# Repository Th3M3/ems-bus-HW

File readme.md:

### EMS Bus Level Shifter PCB

##### Stückliste:

| Bez.| Typ        | Bauform  | Reichelt.de Bezeichnung                         | Artikel-Nr.       |
| --- | ---------- | -------- | ------------------------------------------------ | ----------------- |
| C1  | 68p/50V    | G0603    | SMD-Kerko, 0603, 68pF, 50V, 5%, MLCC             | NPO 0603 BF 68P   |
| C2  | 10µ/25V    | G0603    | SMD-Vielschichtkondensator G0603 - 10µF 25V      | X5R-G0603 10/25   |
| C3  | 1n/50V     | G0603    | SMD-Kerko, 0603, 1,0nF, 50V, 10%, MLCC           | X7R 0603 CF 1,0N  |
| C4  | 1.5n/50V   | G0603    | SMD-Kerko, 0603, 1,5nF, 50V, 10%, MLCC           | X7R 0603 CF 1,5N  |
| C5  | 10n/50V    | G0603    | SMD-Vielschicht-Keramikkondensator 10N, 10%      | X7R-G0603 10N     |
| C6  | 100n/50V   |G0603     | SMD-Kerko, 0603, 100nF, 50V, 10%, MLCC, FT-Cap   | X7R 0603FCF 100N  |
| D1  | BAT42      | MINIMELF | Schottkydiode, 30 V, 0,2 A, Mini Melf            | BAT 42 SMD        |
| D2  | BAT42      | MINIMELF | Schottkydiode, 30 V, 0,2 A, Mini Melf            | BAT 42 SMD        |
| D3  | BAT42      | MINIMELF | Schottkydiode, 30 V, 0,2 A, Mini Melf            | BAT 42 SMD        |
| D4  | BAT42      | MINIMELF | Schottkydiode, 30 V, 0,2 A, Mini Melf            | BAT 42 SMD        |
| D5  | BAT42      | MINIMELF | Schottkydiode, 30 V, 0,2 A, Mini Melf            | BAT 42 SMD        |
| D6  | 1N4148     | MINIMELF | Gleichrichterdiode, 100 V, 0,15 A, Mini Melf     | 1N 4148 SMD       |
| F1  | 30V/150mA  | 1210     | Rückstellende Sicherungen, 30 V, 150 mA          | LITT MICROSMD005  |
| F2  | 30V/150mA  | 1210     | Rückstellende Sicherungen, 30 V, 150 mA          | LITT MICROSMD005  |
| IC1 | LM393 SMD  | SOIC-8   | Komparator, 2-fach, SO-8                         | LM 393 D SMD      |
| L1  | 4,7µH      | 1206     | SMD-Induktivität, 1206, Ferrit, 4,7µ             | L-1206F 4,7µ      |
| L2  | 4,7µH      | 1206     | SMD-Induktivität, 1206, Ferrit, 4,7µ             | L-1206F 4,7µ      |
| R1  | 10k        | R0805    | SMD-Widerstand, 0805, 10 kOhm, 125 mW, 1%        | RND 0805 1 10K    |
| R2  | 360R       | R0805    | SMD-Widerstand, 0805, 360 Ohm, 125 mW, 1%        | RND 0805 1 360    |
| R3  | 47k        | R0805    | SMD-Widerstand, 0805, 47 kOhm, 125 mW, 1%        | RND 0805 1 47K    |
| R5  | 100k       | R0805    | SMD-Widerstand, 0805, 100 kOhm, 125 mW, 1%       | RND 0805 1 100K   |
| R6  | 4.7k       | R0805    | SMD-Widerstand, 0805, 4,7 kOhm, 125 mW, 1%       | RND 0805 1 4,7K   |
| R7  | 100R       | R0805    | SMD-Widerstand, 0805, 100 Ohm, 125 mW, 1%        | RND 0805 1 100    |
| R8  | 910R       | R0805    | SMD-Widerstand, 0805, 910 Ohm, 125 mW, 1%        | RND 0805 1 910    |
| R9  | 910R       | R0805    | SMD-Widerstand, 0805, 910 Ohm, 125 mW, 1%        | RND 0805 1 910    |
| R10 | 910R       | R0805    | SMD-Widerstand, 0805, 910 Ohm, 125 mW, 1%        | RND 0805 1 910    |
| R11 | 910R       | R0805    | SMD-Widerstand, 0805, 910 Ohm, 125 mW, 1%        | RND 0805 1 910    |
| R12 | 4.7k       | R0805    | SMD-Widerstand, 0805, 4,7 kOhm, 125 mW, 1%       | RND 0805 1 4,7K   |
| T1  | BC847B     | SOT-23   | Bipolartransistor, NPN, 45V, 0,1A, 0,25W, SOT-23 | BC 847B INF       |

---
##### Changelog:
- v2:
   * verbesserte Teileplazierung auf der Platine
   * breitere Leiterbahnen an der Thermal Pads
   * größere Schrift 'EMS Bus Level Shifter'

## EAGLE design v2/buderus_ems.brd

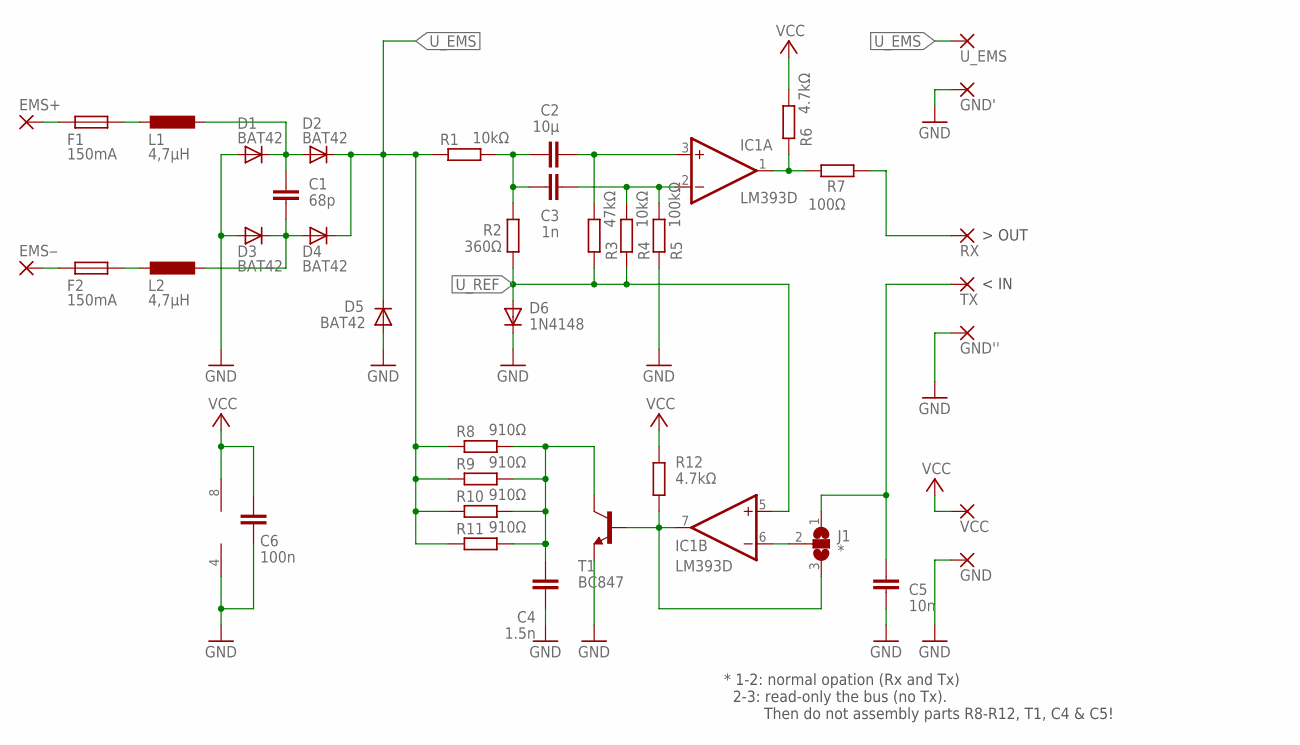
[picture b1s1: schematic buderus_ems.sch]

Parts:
C1: 68p; C0603
C2: 10µ; C0603
C3: 1n; C0603
C4: 1.5n; C0603
C5: 10n; C0603
C6: 100n; C0603
D1, D2, D3, D4, D5: BAT42; MINIMELF
D6: 1N4148; MINIMELF
EMS+: WIREPAD2,15/1,0; 2,15/1,0
EMS‒: WIREPAD2,15/1,0; 2,15/1,0
F1, F2: 150mA; R1210
GND: WIREPAD2,15/1,0; 2,15/1,0
GND': WIREPAD2,15/1,0; 2,15/1,0
GND'': WIREPAD2,15/1,0; 2,15/1,0
IC1: LM393D; SO08
J1: *; SJ_2
L1, L2: 4,7µH; L3216C
R1, R4: 10kΩ; R0805
R2: 360Ω; R0805
R3: 47kΩ; R0805
R5: 100kΩ; R0805
R6, R12: 4.7kΩ; R0805
R7: 100Ω; R0805
R8, R9, R10, R11: 910Ω; R0805
RX: WIREPAD2,15/1,0; 2,15/1,0
T1: BC847; SOT23
TX: WIREPAD2,15/1,0; 2,15/1,0
U_EMS: WIREPAD2,15/1,0; 2,15/1,0
VCC: WIREPAD2,15/1,0; 2,15/1,0

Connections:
EMS_1: C1.2, D1.C, D2.A, L1.2
EMS_2: C1.1, D3.C, D4.A, L2.2
EMS_RX: R7.1, RX.1
EMS_TX: C5.2, J1.1, TX.1
GND: C4.1, C5.1, C6.1, D1.A, D3.A, D5.A, D6.C, GND.1, GND'.1, GND''.1, IC1.4 (V-), R5.1, T1.2 (E)
unnamed: IC1.7 (OUT), J1.3, R12.1, T1.1 (B)
unnamed: IC1.6 (-IN), J1.2
unnamed: C3.2, IC1.2 (-IN), R4.2, R5.2
unnamed: C2.2, IC1.3 (+IN), R3.2
unnamed: IC1.1 (OUT), R6.1, R7.2
unnamed: EMS+.1, F1.1
unnamed: EMS‒.1, F2.1
unnamed: C4.2, R8.2, R9.2, R10.2, R11.2, T1.3 (C)
unnamed: F1.2, L1.1
unnamed: F2.2, L2.1
unnamed: C2.1, C3.1, R1.2, R2.2
U_EMS: D2.C, D4.C, D5.C, R1.1, R8.1, R9.1, R10.1, R11.1, U_EMS.1
U_REF: D6.A, IC1.5 (+IN), R2.1, R3.1, R4.1
VCC: C6.2, IC1.8 (V+), R6.2, R12.2, VCC.1

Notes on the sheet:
* 1-2: normal opation (Rx and Tx) 2-3: read-only the bus (no Tx). Then do not assembly parts R8-R12, T1, C4 & C5!
< IN

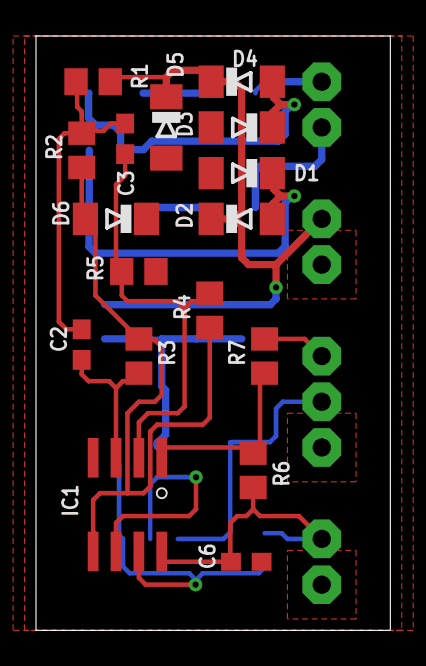
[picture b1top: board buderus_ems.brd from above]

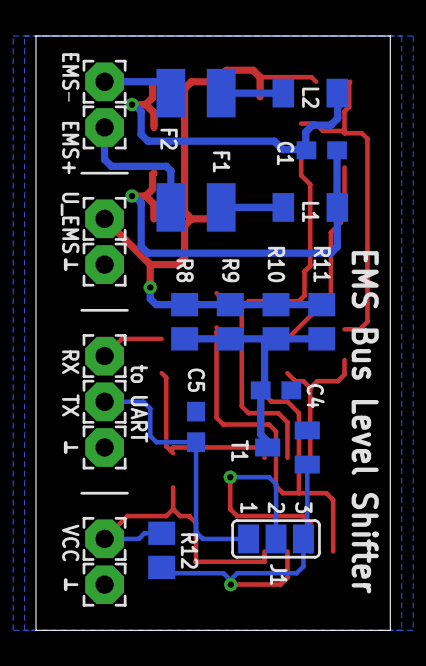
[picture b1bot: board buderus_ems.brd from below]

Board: 2 copper layers, 19.7 x 33.0 mm, 40 parts (23 on the bottom side), 19 nets.

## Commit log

2019-01-21 add files
2019-01-21 add readme
